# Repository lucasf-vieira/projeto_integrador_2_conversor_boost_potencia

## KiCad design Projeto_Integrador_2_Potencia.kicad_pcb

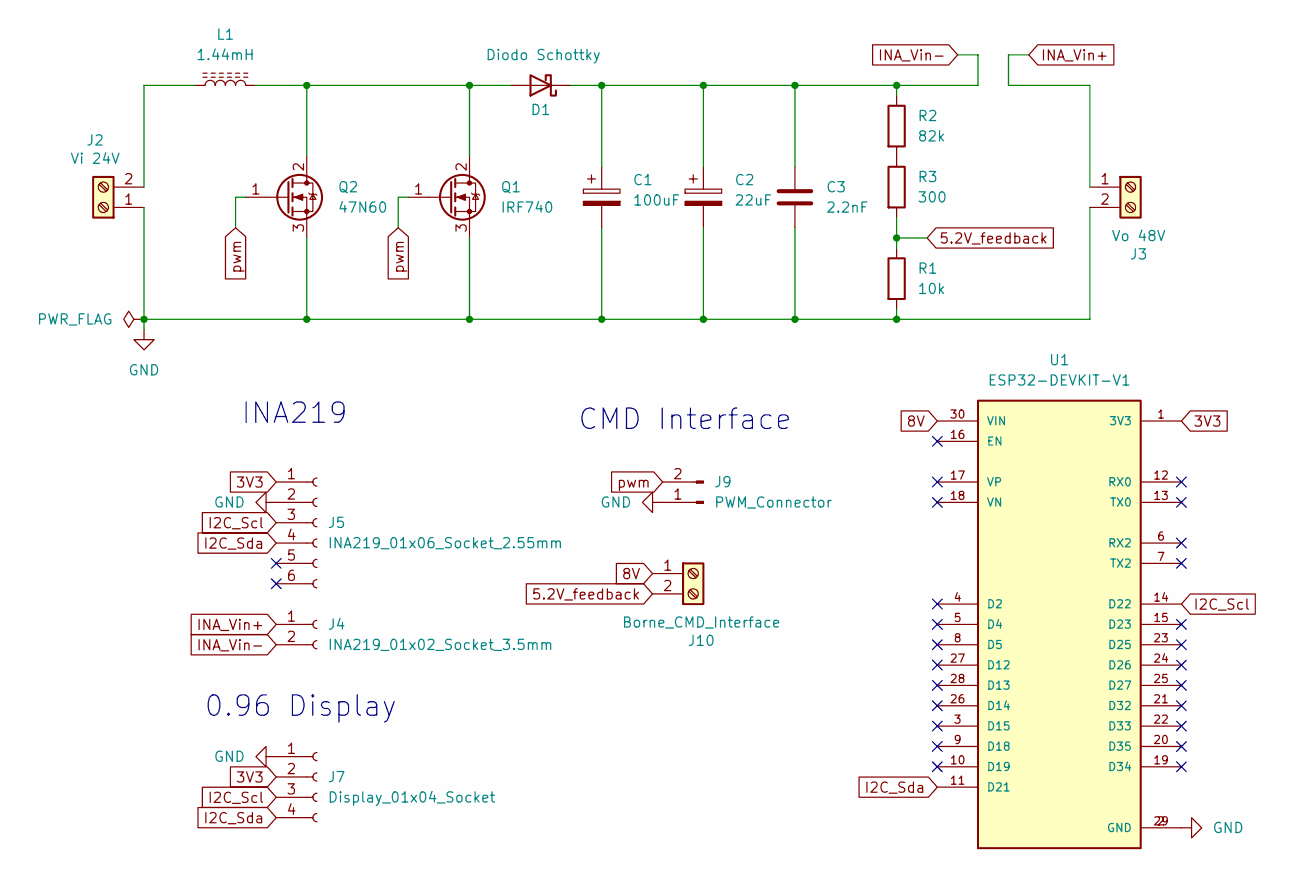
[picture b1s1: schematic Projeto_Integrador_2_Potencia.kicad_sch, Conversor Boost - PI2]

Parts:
C1: 100uF; CP_Radial_D10.0mm_P7.50mm
C2: 22uF; CP_Radial_D5.0mm_P2.50mm
C3: 2.2nF; C_Disc_D3.0mm_W2.0mm_P2.50mm
D1: Diodo Schottky; D_A-405_P10.16mm_Horizontal
J2: Vi 24V; TerminalBlock_Xinya_XY308-2.54-2P_1x02_P2.54mm_Horizontal
J3: Vo 48V; TerminalBlock_Xinya_XY308-2.54-2P_1x02_P2.54mm_Horizontal
J4: INA219_01x02_Socket_3.5mm; TerminalBlock_4Ucon_1x02_P3.50mm_Horizontal
J5: INA219_01x06_Socket_2.55mm; PinSocket_1x06_P2.54mm_Vertical
J7: Display_01x04_Socket; PinSocket_1x04_P2.54mm_Vertical
J9: PWM_Connector; JST_EH_B2B-EH-A_1x02_P2.50mm_Vertical
J10: Borne_CMD_Interface; TerminalBlock_Xinya_XY308-2.54-2P_1x02_P2.54mm_Horizontal
L1: 1.44mH; L_Axial_L29.9mm_D14.0mm_P38.00mm_Horizontal_Vishay_IHA-105
Q1: IRF740; TO-220-3_Vertical
Q2: 47N60; TO-247-3_Vertical
R1: 10k; R_Axial_DIN0207_L6.3mm_D2.5mm_P10.16mm_Horizontal
R2: 82k; R_Axial_DIN0207_L6.3mm_D2.5mm_P10.16mm_Horizontal
R3: 300; R_Axial_DIN0207_L6.3mm_D2.5mm_P10.16mm_Horizontal
U1: ESP32-DEVKIT-V1; MODULE_ESP32_DEVKIT_V1; PARTREV N/A

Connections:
3V3: J5.1, J7.2, U1.1 (3V3)
5.2V_feedback: J10.2, R1.1, R3.2
8V: J10.1, U1.30 (VIN)
GND: C1.2, C2.2, C3.2, J2.1, J3.2, J5.2, J7.1, J9.1, Q1.3 (S), Q2.3 (S), R1.2, U1.2 (GND), U1.29 (GND)
I2C_Scl: J5.3, J7.3, U1.14 (D22)
I2C_Sda: J5.4, J7.4, U1.11 (D21)
INA_Vin+: J3.1, J4.1
INA_Vin-: C1.1, C2.1, C3.1, D1.1 (K), J4.2, R2.1
unnamed: D1.2 (A), L1.2, Q1.2 (D), Q2.2 (D)
unnamed: J2.2, L1.1
unnamed: R2.2, R3.1
pwm: J9.2, Q1.1 (G), Q2.1 (G)

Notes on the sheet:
0.96 Display
CMD Interface
INA219

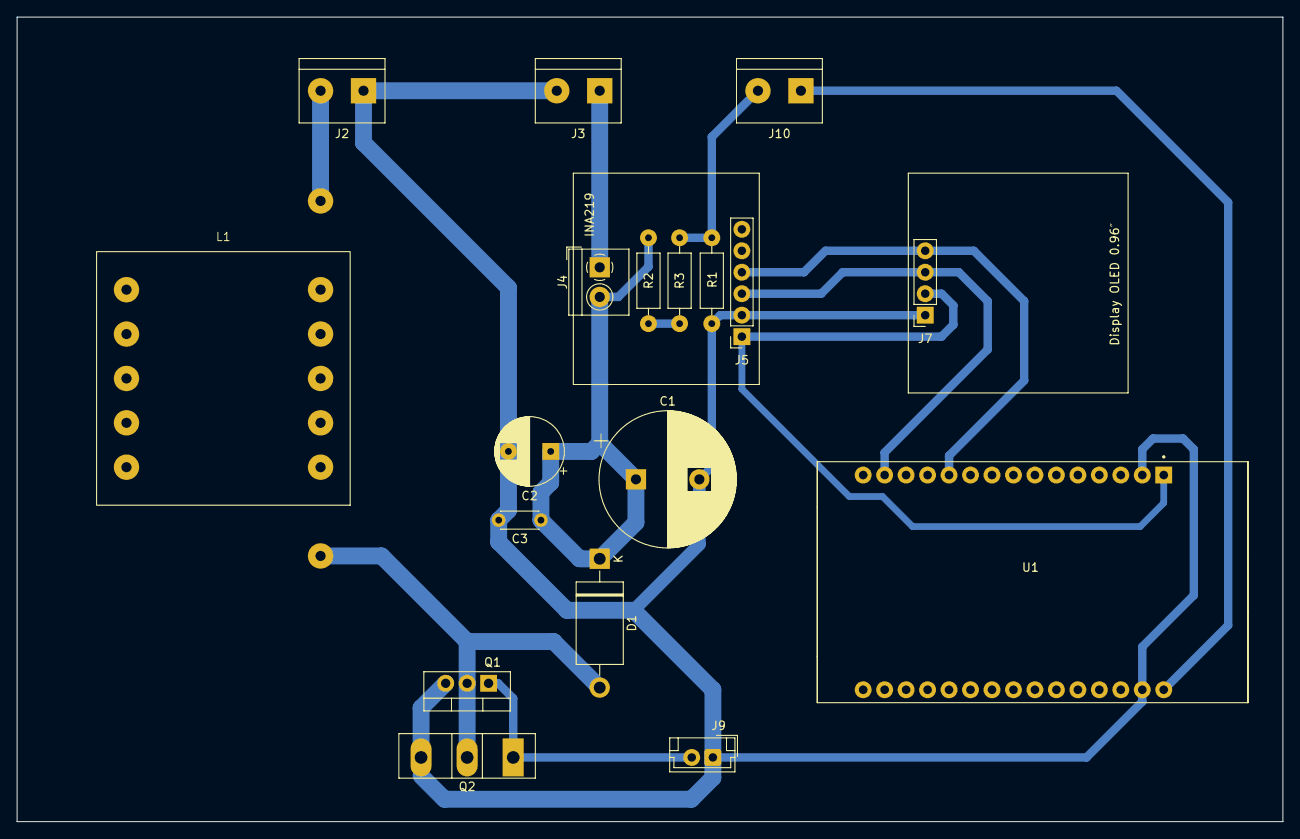
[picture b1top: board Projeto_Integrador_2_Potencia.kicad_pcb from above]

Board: 2 copper layers, 149.7 x 95.2 mm, 18 parts (0 on the bottom side), 12 nets.

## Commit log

2024-10-18 Adiciona arquivos do projeto. Ainda falta fazer o layout do conversor
2024-10-19 Inclusão dos soquetes para ESP32 e INA219
    -Alimentação 12V para o ESP32
    -Alimentação 3V3 do ESP32 para o INA
    -Divisor de tensão de 48V para 5V2 para Feedback para Circuito de Comando
    Falta desenvolver Layout
2024-10-19 Esquemático Finalizado + Começo Layout
    -Precisa confirmar tamanho do Indutor
    -Precisa Trocar mosfet de lugar(devido ao dissipador)
    -Ao definir locais de componentes, fazer trilhas
2024-10-20 Aplicação de recomendações Texas Instruments para layout e disposição de trilhas
2024-10-23 Adição de footprint e símbolo do ESP32
    Atualização das trilhas da PCB
2024-10-23 Correções do layout da pcb e alinhamento do grupo
2024-10-30 Adição de recuo nas bordas do layout
2024-11-08 Mudanças após primeira manufatura
2024-11-09 Alargamento de trilhas e pads
    Correção do valor do capacitor cerâmico
2024-11-11 Remoção de arquivos desnecessários ao git
2024-11-11 Adição de .gitignore para projetos KiCad
2024-11-11 Remoção das zonas de cobre
2024-11-12 MQTT e WiFi implementados
2024-11-23 implementacao INA219, Display e MOCK
2024-11-27 adaptacao da taxa de transmissão
